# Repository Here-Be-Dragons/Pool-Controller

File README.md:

# Automated Pool Controller
###### Timer Control of a Hayward Tristar VS Pump and Hayward GL-235 Solar Pool Controller

### Overview
---------------------
**Background:**
Due to the engineering principle known as the Pump Affinity Law (<https://en.wikipedia.org/wiki/Affinity_laws>), a very significant energy savings can be had by reducing the speed at which you run your pool pump (approaching 90% savings in an optimal configuration vs. a single-speed pump).  The ideal configuration for energy savings would be to run a pump 24-hours a day at the lowest setting possible to still achieve desired water pumping volume (rule of thumb: 1 pool's water turnover per day), with needed speed-ups at various points during your day to enable the skimmer/vacuum/etc to function.  

My solar heat controller, the Hayward GL-235, actuates a valve to enable or disable the solar panels based on the delta of water temp vs. roof temp, and a maximum temperature setting on the controller itself.  Additionally, according to Hayward, minimum flow for optimal water heating once prime is achieved is 5GPM per panel.  I have 9 panels, so an optimal flow through the solar collectors is 45GPM.  

I do not have a Vacuum system, or other systems that require specific or minimum speed settings.

**The Problem:**
You never know when solar heating will be available.  One day the controller could be calling for heat from 10am to 5pm, and the next it could never reach the delta needed to activate.  Therefore, we need a way to alert the pump to run at the minimum specified speed.

**The Solution:**
An arduino-based butt device called the Particle Photon, with a break-out relay board to activate each of the 3 relays to control speed.  

Code requirements:
-   Easily modified timing
-   Interruptible via buttons+display at controller and/or via phone app (SmartThings)
-   Automatic schedule recovery after a power outage
-   Automatic speed for Solar heater
-   Tracking of a number of values related to the pool:
    -   Water temperature before solar heating
    -   Water temperature after solar heating
    -   Roof temperature
    -   Total kWh used per day
    -   Total gallons pumped per day

The Hayward Tristar VS pool pump has a "third party controls" function that allows you to request a speed based on a combination of 3 relays.  Additionally, the Hayward GL-235 has a relay intended to to trigger a booster pump.  Using both of these facts:  

| Timer Speed | STEP 1 Status | STEP 2 Status | STEP 3 Status |
| ----------- | ------------- | ------------- | ------------- |
| 1           | OFF           | OFF           | OFF           |
| 2           | ON            | OFF           | OFF           |
| 3           | OFF           | ON            | OFF           |
| 4           | ON            | ON            | OFF           |
| 5           | OFF           | OFF           | ON            |
| 6           | ON            | OFF           | ON            |
| 7           | OFF           | ON            | ON            |
| 8           | ON            | ON            | ON            |

The STEP inputs have very wide allowed voltages per the User Manual:
> Inputs are rated to accept a low voltage supply of 18-30VAC (24VAC+/-20%) or 9-30VDC (12/24VDC +/-20%).

Hayward recommends taking power from +12V output to pump controller on RS485 connection as relay source power. "ICOM" (ground) would be jumpered to COM on RS485, so 4-wire connection to the Particle Photon would be:
1.  +12VDC (RS485) &lt;= (White wire) =&gt; Relay inputs
2.  STEP 1 (Relay) &lt;= (Blue wire) =&gt; Relay output
3.  STEP 2 (Relay) &lt;= (Brown wire) =&gt; Relay output
4.  STEP 3 (Relay) &lt;= (Black wire) =&gt; Relay output
    With a 5th internal jumper:
5.  RS485 COM &lt;= =&gt; Digital Input ICOM

(My 4/c wire is white/blue/brown/black)  

From the Photon, I have a wire that runs through the Solar Controller's booster pump relay (I do not have a booster pump) back to an INPUT pin with pulldown circuitry.  This allows the Photon to know when the solar collectors are active and react accordingly.  

Lastly, I have a number of variables made available for my Grafana dashboard with metrics gathered by Collectd:
-   Speed
-   Wattage
-   Flow
-   Solar activity
-   Temperature of pool
-   Temperature after solar
-   Temperature of roof

The first 3 of these are reliant on correct tables in the top of the Photon's code.

### Parts:
-------------------
-   5v-controlled relay with 4 separate relay ports (something like SainSmart 4-Channel Relay Module, <http://www.amazon.com/SainSmart-101-70-101-4-Channel-Relay-Module/dp/B0057OC5O8>)
-   Particle Photon
-   22AWG 4/C 300v wire (Connected to Pump)
-   22AWG 2/C 300v wire (Connected to Solar Controller)
-   0.96" 128x64 SPI/I<sup>2</sup>C OLED Display Module for Arduino (aliexpress.com)
-   Custom printed PCB from Osh Park: https://oshpark.com/shared_projects/181LS60Z
-   10k photoresistor
-   4 2-pin headers
-   4 push buttons
-   Barrel jack connector
-   Various resistors (identified in eagle/Pool_Controller.sch)

### Configuration of code:
-------------------------------------
**speedRPM\[8\]:** Make necessary configurations via the pump controls for speeds you chose, then update the code's array with the pump's speeds.  This ensures proper display values on the OLED, and to any web interfaces/dashboards.

**energyConsum\[8\]:** This is variable based on your installation (head pressure, pipe diameter, etc).  Trigger each configured speed and allow it to stabilize, then record the pump display’s wattage indication to the code's array.

**flowCalc\[8\]:** If you have a flow meter, great, use that.  If not, an estimation can be made using mas985's spreadsheet calculator from the Trouble Free Pools forum.  You can get the latest copy from the below URL.  You want "Pool Pump Tools".
<http://www.troublefreepool.com/threads/830-Hydraulics-101-Have-you-lost-your-head?p=6231&amp;viewfull=1#post6231>

### Other Notes:
-------------------------
**GL-235 Specifics:**  
Do not use the relay on the right side, instead use the one designed for starting a booster pump.  The one on the right side injects 20VAC into the line.

**Data Tracking:**
I have data tracked/graphed using the following:
-   Grafana + InfluxDB + Collectd:
    -   Collectd uses the `curl_json` plugin to query the `pumpSpeed`, `pumpWattage`, `waterFlow`, `solarAct`, and `override` variables
    -   Collectd uses the `network` plugin to output the results to an InfluxDB TSD
    -   Grafana displays the results on a dashboard.
    -   This requires a Linux device running somewhere.  It does not need to have any ports accessible to the internet since it is pulling the data.
    -   See collectd/pool-controller.conf and grafana/pool-controller.json for relevant configuration examples.
-   Google Documents: Particle.Publish() -> IFTTT Recipe -> Google Drive
    -   Recipe example:
        -   If (Event Name): `24Hr_kWh`
        -   is (Event Contents): <Leave Blank>
        -   Device Name or ID: Particle Device being used
        -   Add row to spreadsheet
    -   This is done to track daily power usage and daily gallons pumped.

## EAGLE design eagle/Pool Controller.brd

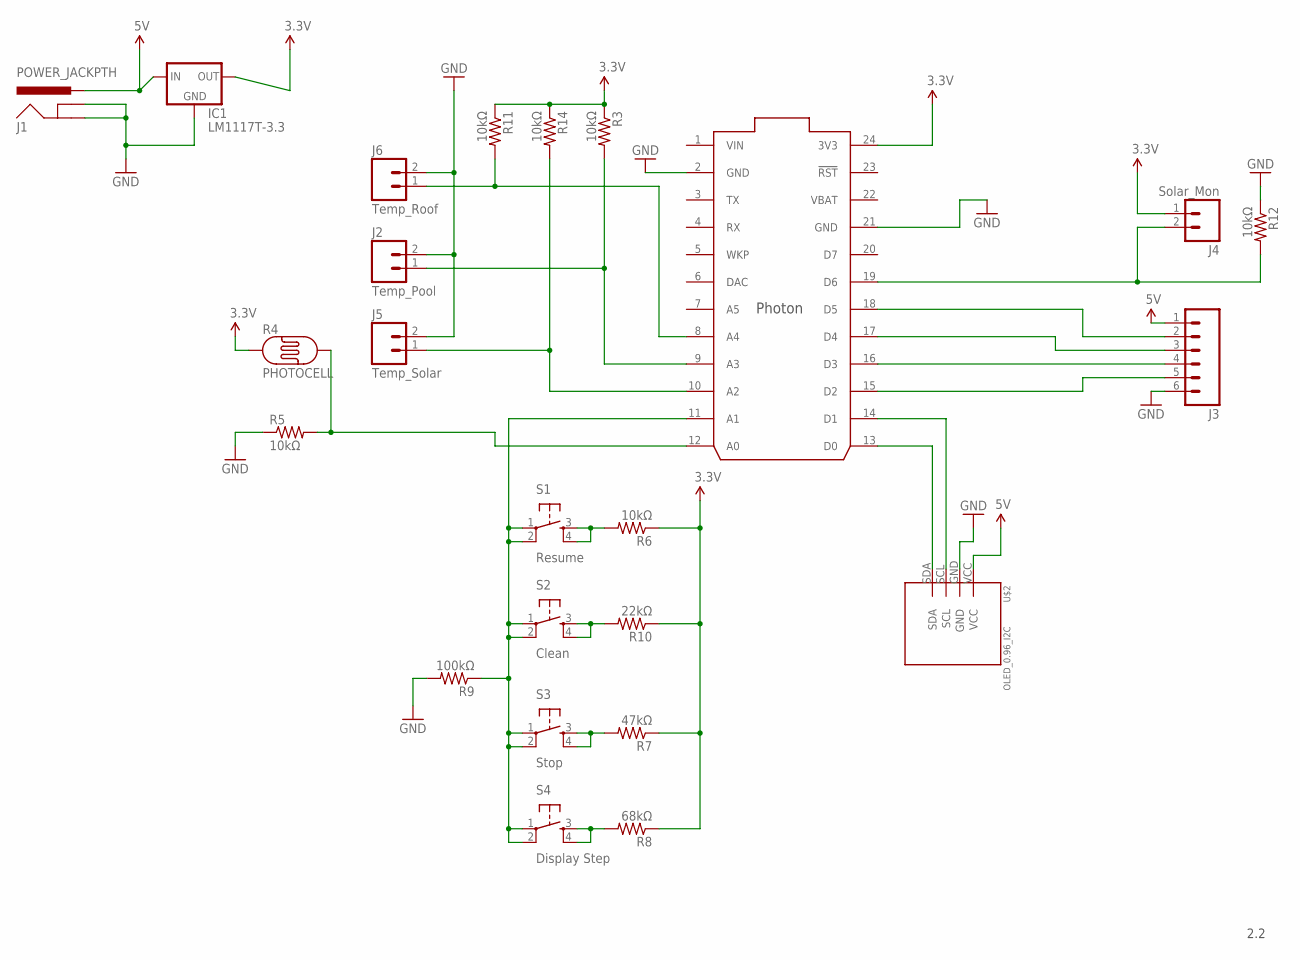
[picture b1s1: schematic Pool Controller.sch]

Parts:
IC1: LM1117T-3.3; TO220V
J1: POWER_JACKPTH; POWER_JACK_PTH
J2: Temp_Pool; SCREWTERMINAL-5MM-2
J3: M06SILK_FEMALE_PTH; 1X06
J4: Solar_Mon; SCREWTERMINAL-5MM-2
J5: Temp_Solar; SCREWTERMINAL-5MM-2
J6: Temp_Roof; SCREWTERMINAL-5MM-2
PHOTON: PHOTON_WITH_HEADERS; PHOTON
R3, R5, R6, R11, R12, R14: 10kΩ; AXIAL-0.3
R4: PHOTOCELL
R7: 47kΩ; AXIAL-0.3
R8: 68kΩ; AXIAL-0.3
R9: 100kΩ; AXIAL-0.3
R10: 22kΩ; AXIAL-0.3
S1: Resume; TACTILE-PTH
S2: Clean; TACTILE-PTH
S3: Stop; TACTILE-PTH
S4: Display Step; TACTILE-PTH
U$2: OLED_0.96_I2C

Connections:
3.3V: IC1.2 (OUT), J4.1, PHOTON.24 (3V3), R3.P$1 (1), R4.1, R6.P$1 (1), R7.P$1 (1), R8.P$1 (1), R10.P$1 (1), R11.P$1 (1), R14.P$1 (1)
5V: IC1.3 (IN), J1.PWR, J3.1, U$2.VCC
GND: IC1.1 (GND), J1.GND, J1.GNDBREAK, J2.2, J3.6, J5.2, J6.2, PHOTON.2 (GND), PHOTON.21 (GND), R5.P$1 (1), R9.P$2 (2), R12.P$1 (1), U$2.GND
unnamed: J3.5, PHOTON.15 (D2)
unnamed: J3.4, PHOTON.16 (D3)
unnamed: PHOTON.13 (D0), U$2.SDA
unnamed: PHOTON.14 (D1), U$2.SCL
unnamed: PHOTON.12 (A0), R4.2, R5.P$2 (2)
unnamed: J3.3, PHOTON.17 (D4)
unnamed: J3.2, PHOTON.18 (D5)
unnamed: R7.P$2 (2), S3.3, S3.4
unnamed: J4.2, PHOTON.19 (D6), R12.P$2 (2)
unnamed: R10.P$2 (2), S2.3, S2.4
unnamed: J5.1, PHOTON.10 (A2), R14.P$2 (2)
unnamed: J2.1, PHOTON.9 (A3), R3.P$2 (2)
unnamed: R8.P$2 (2), S4.3, S4.4
unnamed: PHOTON.11 (A1), R9.P$1 (1), S1.1, S1.2, S2.1, S2.2, S3.1, S3.2, S4.1, S4.2
unnamed: R6.P$2 (2), S1.3, S1.4
unnamed: J6.1, PHOTON.8 (A4), R11.P$2 (2)
VBAT: PHOTON.22 (VBAT)
VIN: PHOTON.1 (VIN)

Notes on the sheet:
2.2

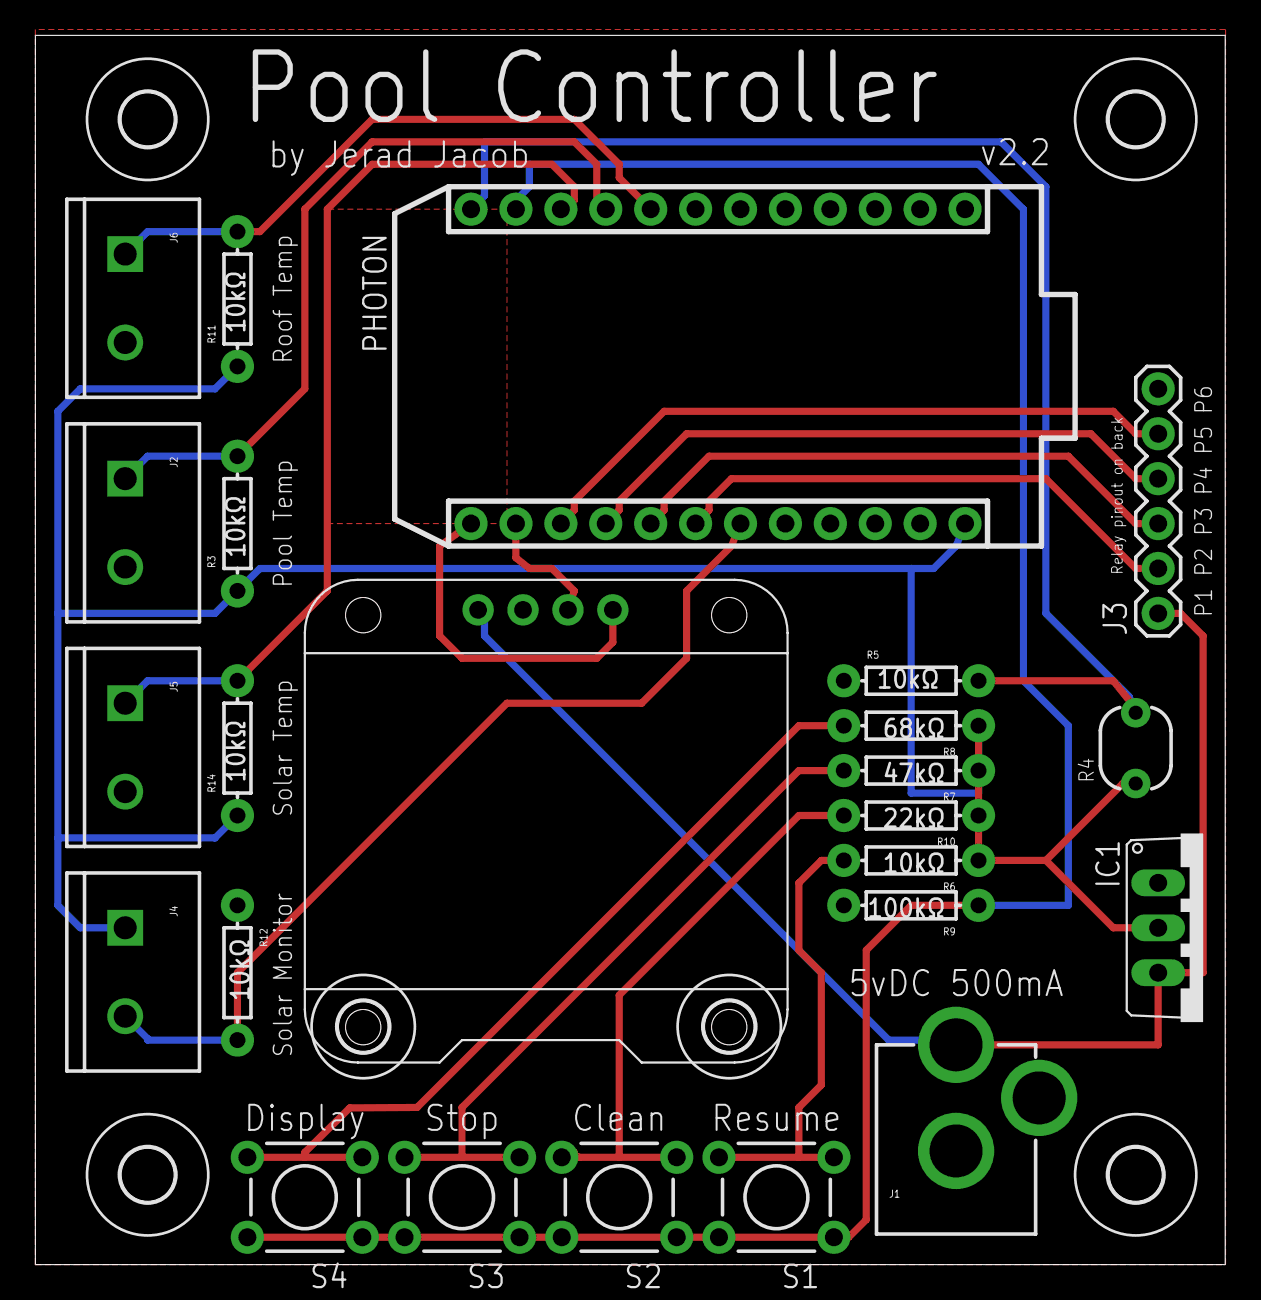
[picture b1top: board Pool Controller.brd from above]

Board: 2 copper layers, 67.3 x 69.5 mm, 30 parts (0 on the bottom side), 19 nets.

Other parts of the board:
U$1, U$7: 2,8
U$3, U$4, U$5, U$6: 3,0

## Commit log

2016-05-14 Partially Complete Device Type
2016-05-14 Partially Complete Sketch
2016-05-14 Framing almost done
2016-05-16 Change to correct file extension
2016-05-18 Latest updates to code
2016-05-19 Latest edits
2016-05-20 First attempt at compilable code
2016-05-20 Fixed compile-time errors. IT COMPILES!!!
2016-05-20 Fixed oled linebreaks
    logic still janky
2016-05-21 First working version!
2016-05-21 Working on midnight loop code
2016-05-23 Still not working
2016-05-26 Still broken but making progress
2016-05-30 Implented accurate time tracking, wattage usage reporting
2016-05-30 Implemented DST, fixed some Epoch conversion bugs
2016-05-30 Working on kWh Reporting
2016-05-31 Rolled back attempt at time formatting
2016-05-31 oled screen formatting
2016-06-05 First working version
    -Keeps a schedule
    -Allows Manual Override
    -Overrides correctly for auto override
    -Hunts for the correct time in the event of an interruption
2016-06-05 Added images folder
2016-06-06 Added thingspeak/Particle Webhook integration
    Tracking Speed and Wattage every 5 minutes
2016-06-06 Added additional instrumentation to ThingSpeak
    -Speed
    -Wattage
    -Flow
    -Solar On/Off
2016-06-06 Initial writeup
2016-06-06 Initial Upload
2016-06-06 Clean up markdown formatting
2016-06-06 Table formatting fix
2016-06-06 formatting
2016-07-05 Thingspeak comments
2016-07-05 Added Gallon tracking to google docs
2016-07-05 Fixed indenting
    maybe spaces will be next
2016-07-05 Updated schedule to never turn pump off
    6am priming of pump was waking me up
2016-07-05 Added info on data logging
2016-07-05 More info on data tracking
2016-07-08 More work on SmartThings. Still broke AF.
2016-08-10 Schedule update
2016-08-10 Added optional override customization to function call
2016-08-10 Fixed OLED to use new overrideEnds function
2016-08-10 Added external antenna call
2016-11-04 Added finished product
2016-11-04 Added particle.variable()
    Allows easy curl commands to pull data into dashboards
2017-02-10 Initial working version of Device Handler
2017-02-10 Major rework
    NEW FEATURES:
    - Now works with SmartThings! Still needs some cleanup to the Device Handler at a later date.
    - Updated README.md with additional screenshot and files for Dashboarding
    BUG FIXES:
    - SmartThings speed selection now works.
2017-03-30 Initial Schematic Design
2017-03-31 Various updates
2017-03-31 Updated Eagle Files
2017-03-31 Finished initial design
2017-03-31 Updated Eagle files for PCB v2.1
2017-03-31 Updated Osh Park renders for v2.1
2017-03-31 Added link to Osh Park
2017-04-01 Added photo sensor tracking
2017-04-03 Added 3 Thermistors and Screen on/off sensor
    Added function from here: http://playground.arduino.cc/ComponentLib/Thermistor2?action=sourceblock&num=3
    We'll see if it works.
2017-04-10 Exclude Eagle files from Linguist
2017-04-11 Added 3.3v Regulator
2017-04-11 Revert "Added 3.3v Regulator"
    This reverts commit 23a2b24274d4a83250f4b2e9a9d27c3bcc80a4d5.
2017-04-12 Initial Rev
2017-04-12 Changed type of tmpButtonState to match buttonState
2017-04-13 corrected relay pinout
2017-04-13 Major Code Rework
    FEATURES:
    - Pool temperature tracking
    - Post-solar temperature tracking
    - Roof temperature tracking
    - OLED turn-off when electrical box is closed
    - Physical button interface to display:
2017-04-13 Moved to Photon-Thermistor library
2017-04-15 Implemented display blanking + bugfixes
    NEW FEATURES
    - Display blanking when dark (door closed)
    BUG FIXES
    - Photoresistor variable value set to uint8_t instead of uint16_t, causing rollover
2017-04-17 Added details
2017-04-21 Added Temps to Dashboard
2017-04-24 Updated Screenshot
2017-04-24 Updated Grafana screenshot
    Added Temps
2017-06-26 Redesign for improved functionality: - Permanent Override - Extended Timed Override - Resume
2017-06-26 Updated for new SmartThings Device Handler
    Added significant featureset to Device Handler for SmartThings
2017-06-26 Typo in previous commit re: adding time
2017-07-07 Cleanup
2017-07-08 Initial layout
2017-07-08 Uncompilable Garbage
    But its *my* uncompilable garbage!
2017-07-08 SmartThings additions
    Compiles
2017-07-09 Working SmartThings with Pump + Solar
    NEW FEATURES:
    - Works with SmartThings Solar Device Type
    BUGFIX:
    - Pump Override Time sent to SmartThings is correct
2017-07-09 Added SmartThings app screenshots
2017-07-09 Working Version
2017-07-09 Removed deprecated DeviceType
    Use `hayward-vs-pool-pump.src` instead
2017-07-09 Fixed 5v to 3v to use Regulator
2017-07-09 Updated render for v2.2 board revision
2017-07-09 Redirected OSHPark URL
    To v2.2 of board to fix regulator
2017-07-09 Removing old board photo
    Replaced with PCB board
2017-07-09 Updated dashboard to output Solar graphs
2017-12-27 Stop logging temps when pump is off

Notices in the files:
parts and their libraries:
SparkFun-Connectors: Licensing: Creative Commons ShareAlike 4.0 International - https://creativecommons.org/licenses/by-sa/4.0
